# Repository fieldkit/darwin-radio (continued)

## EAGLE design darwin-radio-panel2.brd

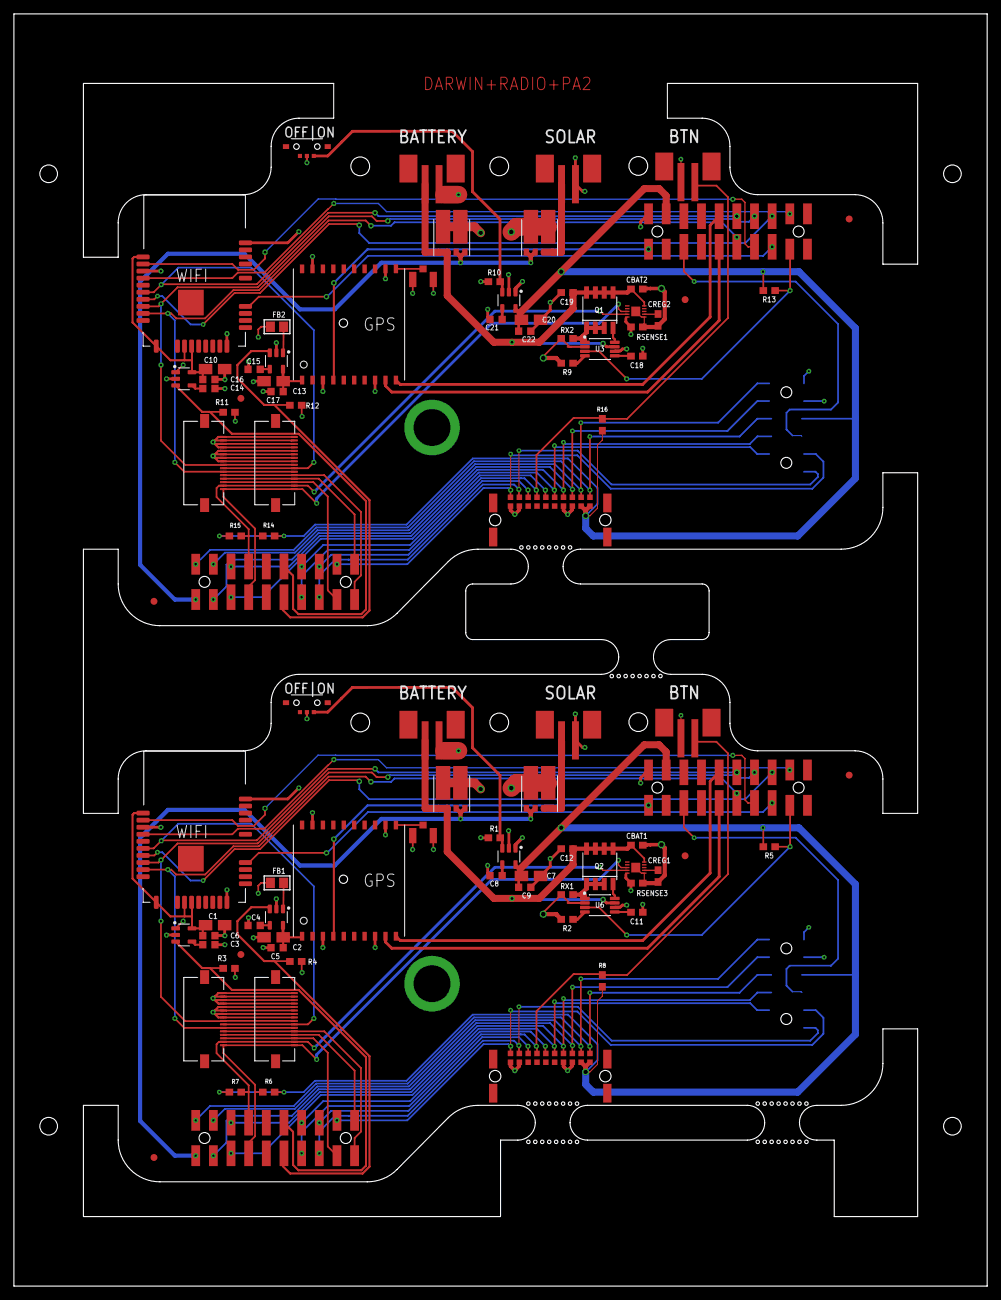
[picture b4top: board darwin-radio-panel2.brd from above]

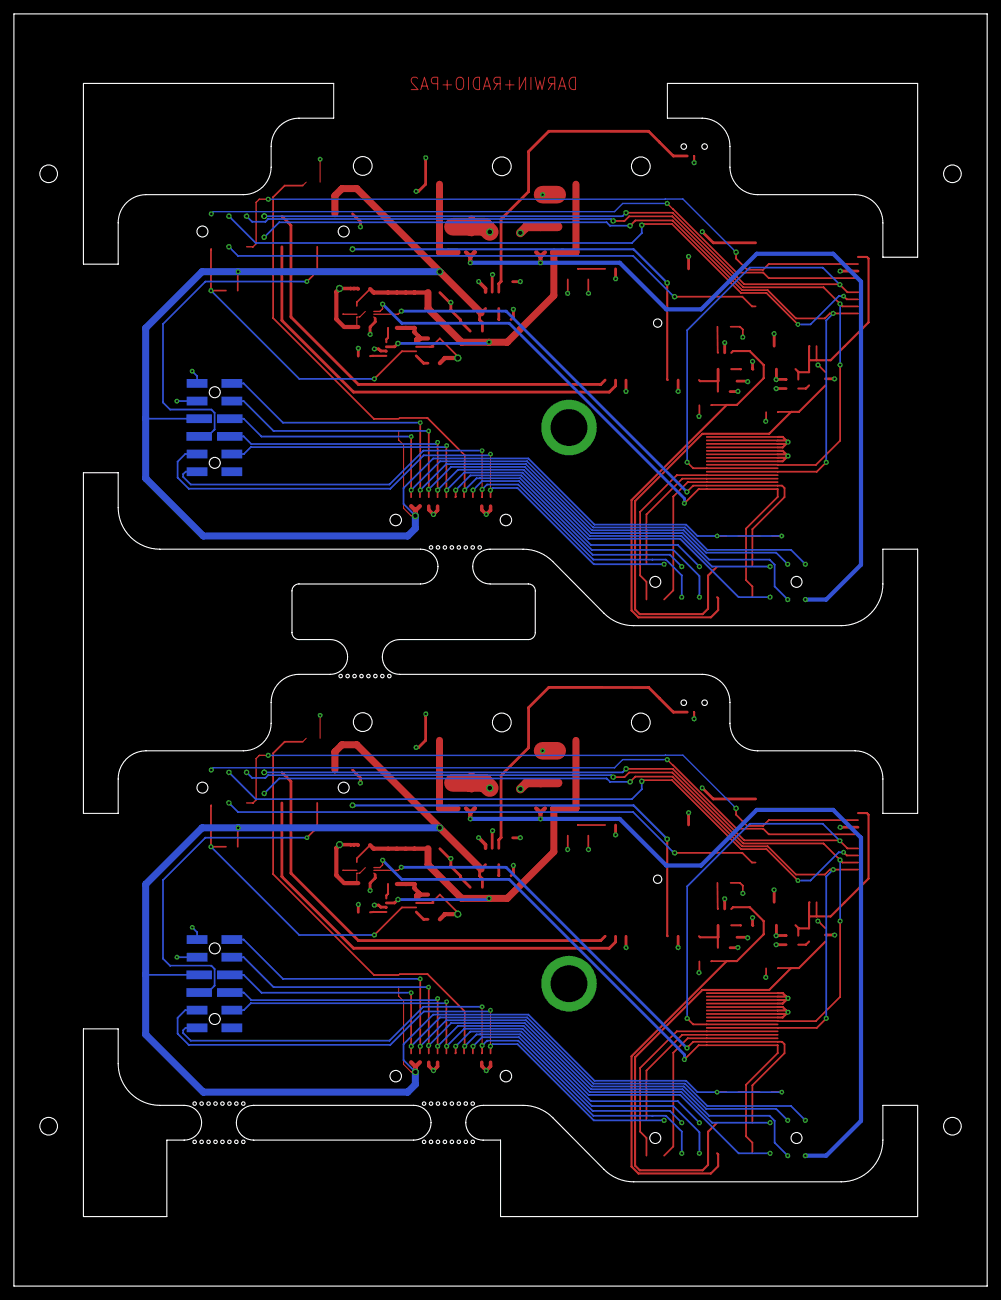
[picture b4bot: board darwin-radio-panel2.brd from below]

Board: 4 copper layers, 140.0 x 183.0 mm, 98 parts (2 on the bottom side), 100 nets.

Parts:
C1, C2, C7, C10, C13, C20: 6.8uf; A/3216-18R
C3, C4, C8, C14, C15, C21: C0603K
C5, C6, C9, C16, C17, C22: .1uf; C0603K
C11, C18: 0.1uF; 0603
C12, C19: 10uF; 0603
CBAT1, CBAT2: 0.1uF; 0603
CREG1, CREG2: 10uF; 0603
D1, D2, D3, D4: V10KL45DUHM3/H
FB1, FB2: 0805
FID1, FID2, FID3, FID4, FID5, FID6, FID7, FID8: FIDUCIAL_1MM
J1, J2, J4, J5: 505110-1692
J3, J6: M55-6102042R
LOWER1, LOWER2: MOLEX-15-91-2200; 20PH
Q1, Q2: NDS8434; SO08-IRF
R1, R2, R3, R4, R5, R6, R7, R8, R9, R10, R11, R12, R13, R14, R15, R16: 100k; 0603
RSENSE1, RSENSE3: 100M; 0603
RX1, RX2: 100M; 0603
U1, U2: ATWINC
U3, U6: MCP7384X; SOP65P490X110-8
U$1, U$10: FGPMMOPA6H; GPS_MODULE
U$2, U$3, U$4, U$13, U$14, U$15: MIC5219-3.3YM5-TR; SOT95P280X145-5
U$5, U$16: SSAJ110100
U$6, U$7, U$9, U$17, U$18, U$22: B2B-PH-SM4-TB
U$8, U$21: 2X6-HEADERSDS; 12PH
U$11, U$20: 2337019-1
U$12, U$19: MAX17055; 10DFN-EP
UPPER1, UPPER2: MOLEX-15-91-2200; 20PH

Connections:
3V1: C20.+, C22.1, J6.P11, J6.P12, R13.1, R14.2, R15.2, R16.1, U$15.5, U$21.3, UPPER2.PIN19
3V3: C7.+, C9.1, J3.P11, J3.P12, R5.1, R6.2, R7.2, R8.1, U$4.5, U$8.3, UPPER1.PIN19
BACKPACK_ENABLE: U$8.4, UPPER1.PIN3
BACKPACK_ENABLE1: U$21.4, UPPER2.PIN3
BAT+: C12.1, CBAT1.1, D1.A1-1, D1.A1-2, Q2.5, Q2.6, Q2.7, Q2.8, U6.7, U$7.+, U$12.P10
BAT+1: C19.1, CBAT2.1, D2.A1-1, D2.A1-2, Q1.5, Q1.6, Q1.7, Q1.8, U3.7, U$18.+, U$19.P10
BAT-: CBAT1.2, CREG1.2, RSENSE3.1, U$7.-, U$12.P6, U$12.PAD
BAT-1: CBAT2.2, CREG2.2, RSENSE1.1, U$18.-, U$19.P6, U$19.PAD
CHARGESUPPLY: D3.K1, D3.K2, R2.1, RX1.1, U6.2
CHARGESUPPLY1: D4.K1, D4.K2, R9.1, RX2.1, U3.2
CHARGING: R5.2, U6.3, UPPER1.PIN9
CHARGING1: R13.2, U3.3, UPPER2.PIN9
EEPROM_PROT: J3.P1, LOWER1.PIN2, U$8.5
EEPROM_PROT1: J6.P1, LOWER2.PIN2, U$21.5
GND: C1.-, C2.-, C3.2, C4.2, C5.2, C6.2, C7.-, C8.2, C9.2, C11.2, C12.2, J1.1, J1.2, J1.3, J1.4, J2.1, J2.2, J2.3, J2.4, J3.P19, J3.P20, R1.1, R3.1, R4.1, RSENSE3.2, U1.9, U1.12, U1.28, U6.6, U$1.P$3, U$1.P$8, U$1.P$12, U$1.P$19, U$2.2, U$3.2, U$4.2, U$6.-, U$8.2, U$9.+, U$11.GND, U$11.GND2, U$12.P5, UPPER1.PIN20
GND1: C10.-, C13.-, C14.2, C15.2, C16.2, C17.2, C18.2, C19.2, C20.-, C21.2, C22.2, J4.1, J4.2, J4.3, J4.4, J5.1, J5.2, J5.3, J5.4, J6.P19, J6.P20, R10.1, R11.1, R12.1, RSENSE1.2, U2.9, U2.12, U2.28, U3.6, U$10.P$3, U$10.P$8, U$10.P$12, U$10.P$19, U$13.2, U$14.2, U$15.2, U$17.-, U$19.P5, U$20.GND, U$20.GND2, U$21.2, U$22.+, UPPER2.PIN20
GPS_ENABLE: LOWER1.PIN16, R4.2, U$2.3
GPS_ENABLE1: LOWER2.PIN16, R12.2, U$13.3
GPS_RX: U$1.P$9, UPPER1.PIN5
GPS_RX1: U$10.P$9, UPPER2.PIN5
GPS_TX: U$1.P$10, UPPER1.PIN16
GPS_TX1: U$10.P$10, UPPER2.PIN16
HOTSWAP_INT: J3.P3, LOWER1.PIN3
HOTSWAP_INT1: J6.P3, LOWER2.PIN3
MOD_G0: J1.13, J2.13, LOWER1.PIN1
MOD_G1: J4.13, J5.13, LOWER2.PIN1
MOD_G2: J3.P2, LOWER1.PIN18, U$8.6
MOD_G3: J6.P2, LOWER2.PIN18, U$21.6
MOD_G4: J6.P5, LOWER2.PIN4
MOD_G5: J3.P5, LOWER1.PIN4
MOD_G6: J4.14, J5.14, LOWER2.PIN19
MOD_G7: J4.12, J5.12, LOWER2.PIN20
MOD_G13: J1.14, J2.14, LOWER1.PIN19
MOD_G14: J1.12, J2.12, LOWER1.PIN20
MOD_MISO: J3.P10, LOWER1.PIN10, U$8.10
MOD_MISO1: J6.P10, LOWER2.PIN10, U$21.10
MOD_MOSI: J3.P8, LOWER1.PIN12, U$8.11
MOD_MOSI1: J6.P8, LOWER2.PIN12, U$21.11
MOD_SCK: J3.P9, LOWER1.PIN9, U$8.12
MOD_SCK1: J6.P9, LOWER2.PIN9, U$21.12
MOD_SCL: J3.P6, LOWER1.PIN13, U$8.8
MOD_SCL1: J6.P6, LOWER2.PIN13, U$21.8
MOD_SDA: J3.P7, LOWER1.PIN8, U$8.9
MOD_SDA1: J6.P7, LOWER2.PIN8, U$21.9
unnamed: C3.1, U$3.4
unnamed: C4.1, U$2.4
unnamed: C2.+, C5.1, U$1.P$1, U$2.5
unnamed: U$1.P$11, U$11.ANT
unnamed: R2.2, U6.4
unnamed: C8.1, U$4.4
unnamed: FB1.2, U$2.1
unnamed: R1.2, U$4.3, U$5.2
unnamed: C14.1, U$14.4
unnamed: C15.1, U$13.4
unnamed: C13.+, C17.1, U$10.P$1, U$13.5
unnamed: Q2.1, Q2.2, Q2.3, RX1.2, U6.1
unnamed: Q1.1, Q1.2, Q1.3, RX2.2, U3.1
unnamed: Q2.4, U6.8
unnamed: C11.1, U6.5
unnamed: CREG1.1, U$12.P7
unnamed: Q1.4, U3.8
unnamed: C18.1, U3.5
unnamed: CREG2.1, U$19.P7
unnamed: R9.2, U3.4
unnamed: C21.1, U$15.4
unnamed: R10.2, U$15.3, U$16.2
unnamed: U$10.P$11, U$20.ANT
unnamed: FB2.2, U$13.1
RADIO_MISO: J1.9, J2.9, U1.17, UPPER1.PIN14
RADIO_MISO1: J4.9, J5.9, U2.17, UPPER2.PIN14
RADIO_MOSI: J1.10, J2.10, U1.15, UPPER1.PIN15
RADIO_MOSI1: J4.10, J5.10, U2.15, UPPER2.PIN15
RADIO_SCK: J1.11, J2.11, U1.18, UPPER1.PIN6
RADIO_SCK1: J4.11, J5.11, U2.18, UPPER2.PIN6
RAD_SCL: J1.16, J2.16, LOWER1.PIN14, R6.1, U$12.P3
RAD_SCL1: J4.16, J5.16, LOWER2.PIN14, R14.1, U$19.P3
RAD_SDA: J1.15, J2.15, LOWER1.PIN7, R7.1, U$12.P4
RAD_SDA1: J4.15, J5.15, LOWER2.PIN7, R15.1, U$19.P4
SOL+: D3.A2-1, D3.A2-2, U$6.+
SOL+1: D4.A2-1, D4.A2-2, U$17.+
UNREG: D1.K1, D1.K2, FB1.1, J1.5, J1.6, J1.7, J1.8, J2.5, J2.6, J2.7, J2.8, J3.P13, J3.P14, U$3.1, U$4.1, U$5.C, U$8.1
UNREG1: D2.K1, D2.K2, FB2.1, J4.5, J4.6, J4.7, J4.8, J5.5, J5.6, J5.7, J5.8, J6.P13, J6.P14, U$14.1, U$15.1, U$16.C, U$21.1
V1: D2.A2-1, D2.A2-2, D4.A1-1, D4.A1-2, LOWER2.PIN11
V5: D1.A2-1, D1.A2-2, D3.A1-1, D3.A1-2, LOWER1.PIN11
VBACKUP: U$1.P$4, UPPER1.PIN1
VBACKUP1: U$10.P$4, UPPER2.PIN1
WIFI_3V1: C10.+, C16.1, U2.10, U2.20, U2.22, U2.23, U$14.5
WIFI_3V3: C1.+, C6.1, U1.10, U1.20, U1.22, U1.23, U$3.5
WIFI_CS: U1.16, UPPER1.PIN13
WIFI_CS1: U2.16, UPPER2.PIN13
WIFI_ENABLE: LOWER1.PIN5, R3.2, U$3.3
WIFI_ENABLE1: LOWER2.PIN5, R11.2, U$14.3
WIFI_IRQ: U1.13, UPPER1.PIN12
WIFI_IRQ1: U2.13, UPPER2.PIN12
WIFI_RST: U1.4, UPPER1.PIN8
WIFI_RST1: U2.4, UPPER2.PIN8
WIFI_WAKE: U1.11, UPPER1.PIN7
WIFI_WAKE1: U2.11, UPPER2.PIN7
XBTN: J3.P4, LOWER1.PIN17, R8.2, U$9.-
XBTN1: J6.P4, LOWER2.PIN17, R16.2, U$22.-

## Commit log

2019-06-10 Basic Lash-Up.
2019-07-05 Fixed Wifi enable, Radio Pullups, BAT+ connection on charger, and internal layer shorts to various vias.
2019-07-05 TA2 CAM files generated.
2019-09-03 Added external button header. added mounting point for single 'backpack' module. Panelized. PA1.
2019-09-30 Cleanup.
2019-09-30 added readme
2020-01-16 Added solar pre-regulation, deprecated fuel gauge, added current sense, replaced current sense resistors, lots of routing changes, new panel.
2020-02-11 Added power switch headers.
2020-02-18 Increased screw hole size and clearance diameter.
2020-02-18 Screw holes to 3.5MM for ANSI-ASME compliance.
2020-05-01 Toughened up connector footprints, cleaned up schematic, added schematic PDF.
2020-08-07 Removed unwanted panel files and changed unpopulated panel template.
2020-08-07 Transitioned from 4 to 2 layers. Added solar power monitor. Changed GPS to L80-M39.
